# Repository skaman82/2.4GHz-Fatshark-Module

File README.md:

BUILD LOG: https://github.com/skaman82/2.4GHz-Fatshark-Module/wiki </br> </br>

# 2.4GHz-Fatshark-Module
RX28 based Fatshark RX module

- 8 channels (2414, 2432, 2450, 2468, 2490, 2510, 2390, 2370 MHz)
- RSSI display
- Fatshark button control
- Bandscan
- Finder mode
- RSSI calibration
- OSD menus
- OLED screen

Tested with following VTX models:</br>
• TBS Unify 2G4</br>
• Lawmate 2.4</br>
• FuriousFPV 2.4 VTX</br>
• Cheap low power chinese transmitter modules </br>
(no audio compatibility issues unlike the latest RX 2.4 module on the market)

# OPERATION
<b>HOME SCREEN:</b> You can change the channels by pressing the UP/DOWN keys - it works also with the google buttons (if the feature is active). If using the joystick you have to press UP/DOWN once to bring the OSD up - then you can change the channel. After no button press is registered the OSD will automatically disappear. </br>
</br>
By pressing the CENTER button you can bring up the <b>MENU</b>. With UP/DOWN you can switch between different menu items. Select EXIT to return to the home screen.</br>
</br>
<b>GOGGLE CONTROL:</b> Enables fatshark button control.</br>
</br>
<b>BANDSCAN:</b> Scans all channels and displays the RSSI values in a graph.</br>
</br>
<b>LOCK MODE:</b> If activated (lock icon in the home screen) the module will lock up after approx. 10 seconds. All controls are disabled to prevent chanel changes on acidental button press. You can temporarily UNLOCK the module by pressing the CENTER button for 3-5 seconds (the lock icon will open). After unlocking the module it will return to locked state after approx. 10 seconds.</br>
</br>
<b>FIND MODE:</b>Will show the RSSI value in a BAR (oled) or a plot (OSD). Depending on the RSSI value the beeper will beep more often and the OSD LED will blink as well indicating the direction. You can change the channel in the FIND MODE - so be sure you have the correct one. Use a directional antenna to find your model with this function.</br>
</br>
<b>AUTOSEARCH:</b> Press the CENTER button for 2 seconds to call the autosearch function. Autosearch will find the strongest channel and switch to it automatically.</br>
</br>
<b>CALIBRATION:</b> You have to run calibration to have the correct RSSI values. Just follow the instructions in the wizzard.</br>

# UPDATING THE FIRMWARE
You will need a FTDI to USB adapter to upload the module firmware. You may need to install the FTDI driver for it. Set the FTDI to 5V.

Steps to upload new firmware
1. Install Arduino IDE
2. Install the Arduino Libraries from the "Libs" folder.
3. Install the MightyCore hardware package from here: https://github.com/MCUdude/MightyCore (just follow the instructions)
4. Download the firmware and open the Code.INO file from the "Code" folder in Arduino
5. Select the hardware settings in Arduino IDE as shown in the image below
6. Connect the FTDI tool according to the plug pinout as shown in the picture and select the COM port in Arduino IDE
7. If you have the rev 06 PCB open the JUMP1 jumper on the PCB to upload code (solder it together after your upload is done).
8. Upload the code </br>
YOU ARE DONE :)

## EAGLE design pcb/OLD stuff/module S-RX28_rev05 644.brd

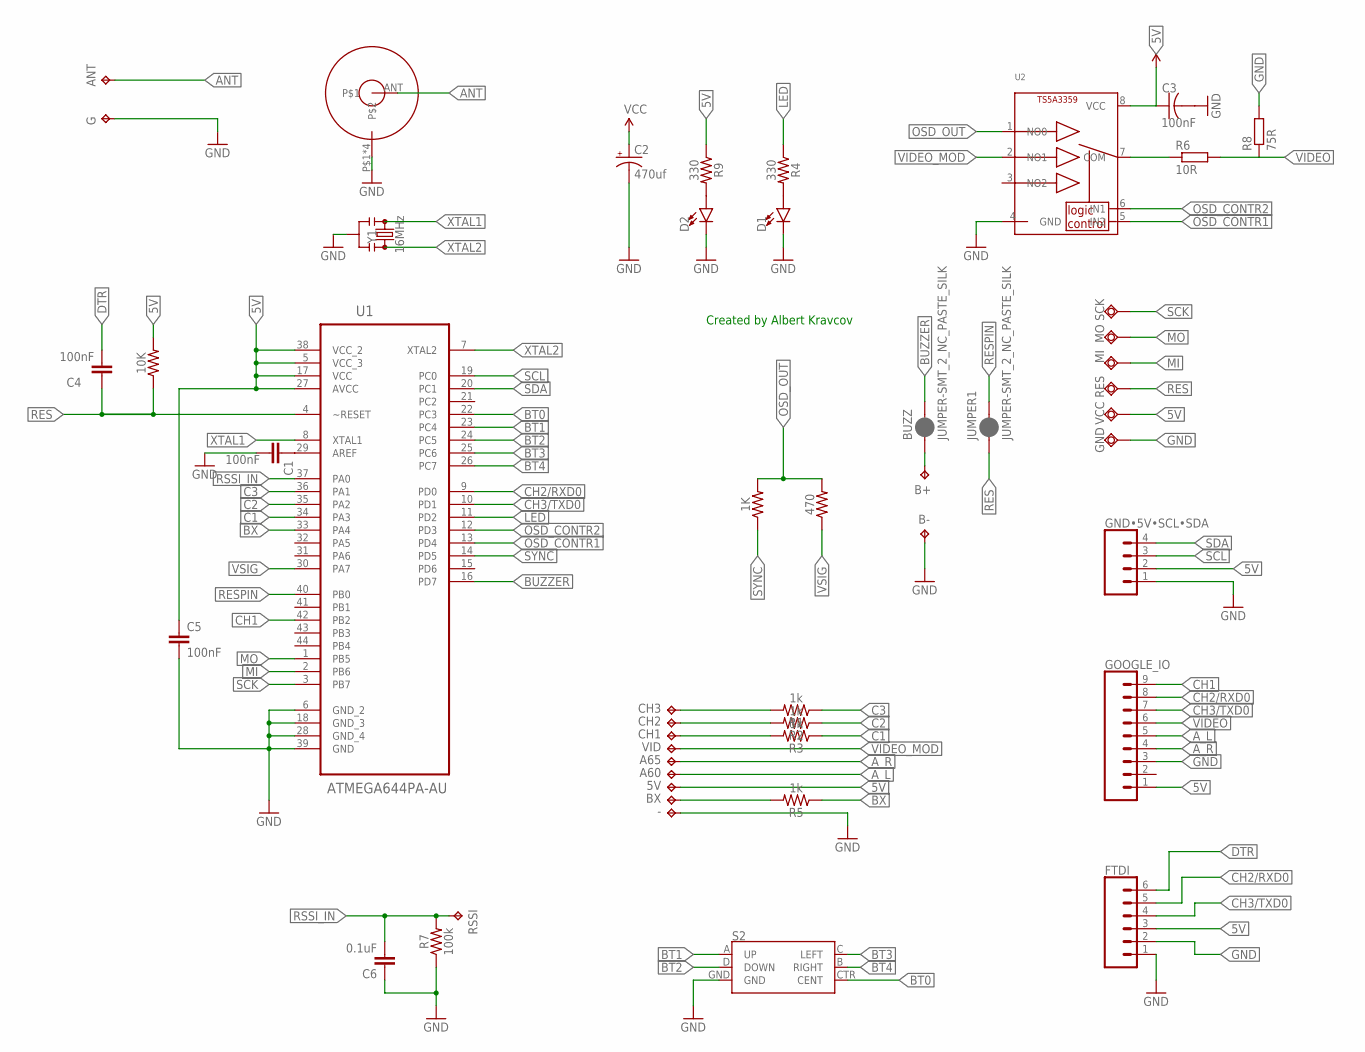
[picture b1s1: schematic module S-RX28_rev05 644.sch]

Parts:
1K, 10K, 470: 0.27OHM-0603-1/10W-1%; 0603
5V: TPTP15SQ; TP15SQ
-: TPTP15SQ; TP15SQ
A60, A65: TPTP15SQ; TP15SQ
ANT: TPTP15R; TP15R
B+: TPTP17SQ; TP17SQ
B-: TPTP17SQ; TP17SQ
BUZZ: JUMPER-SMT_2_NC_PASTE_SILK; SMT-JUMPER_2_NC_PASTE_SILK
BX: TPTP15SQ; TP15SQ
C1, C4, C5: 100nF; 0603
C2: 470uf; EIA7343
C3: 100nF; C0603
C6: 0.1uF; 0603
CH1, CH2, CH3: TPTP15SQ; TP15SQ
D1, D2: LED0603; LED-0603
FTDI: CONN_06SMD-1MM; 1X06-1MM
G: TPTP15SQ; TP15SQ
GND: GND; B1,27
GND•5V•SCL•SDA: CONN_04; 1X04
GOOGLE_IO: CONN_09; 1X09
JUMPER1: JUMPER-SMT_2_NC_PASTE_SILK; SMT-JUMPER_2_NC_PASTE_SILK
MI: TPSQB1,27; B1,27
MO: TPSQB1,27; B1,27
R1, R2, R3, R5: 1k; 0603
R4, R9: 330; 0603
R6: 10R; R0603
R7: 100k; 0603
R8: 75R; R0603
RES: TPSQB1,27; B1,27
RSSI: TPTP15SQ; TP15SQ
S2: JOYSTICK_MINI
SCK: TPSQB1,27; B1,27
U1: ATMEGA644PA-AU; QFP80P1200X1200X120-44N
U2: TS5A3359; VFSOP-8
U$1: SMA_ANTENNA; SMA_CONNECTOR
VCC: TPSQB1,27; B1,27
VID: TPTP15SQ; TP15SQ
Y1: 16MHz; RESONATOR-SMD-3.2X1.3

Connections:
5V: 5V.TP, 10K.2, C2.A (+), C3.1, C5.1, FTDI.3, GND•5V•SCL•SDA.2, GOOGLE_IO.1, R9.1, U1.5 (VCC_3), U1.17 (VCC), U1.27 (AVCC), U1.38 (VCC_2), U2.8 (VCC), VCC.TP
ANT: ANT.TP, U$1.ANT
AREF: C1.1, U1.29 (AREF)
A_L: A60.TP, GOOGLE_IO.5
A_R: A65.TP, GOOGLE_IO.4
BT0: S2.CTR (CENT), U1.22 (PC3)
BT1: S2.A (UP), U1.23 (PC4)
BT2: S2.D (DOWN), U1.24 (PC5)
BT3: S2.C (LEFT), U1.25 (PC6)
BT4: S2.B (RIGHT), U1.26 (PC7)
BUZZER: BUZZ.2, U1.16 (PD7)
BX: R5.1, U1.33 (PA4)
C1: R3.1, U1.34 (PA3)
C2: R2.1, U1.35 (PA2)
C3: R1.1, U1.36 (PA1)
CH1: GOOGLE_IO.9, U1.42 (PB2)
CH2/RXD0: FTDI.5, GOOGLE_IO.8, U1.9 (PD0)
CH3/TXD0: FTDI.4, GOOGLE_IO.7, U1.10 (PD1)
DTR: C4.2, FTDI.6
GND: -.TP, B-.TP, C1.2, C2.C (-), C3.2, C5.2, C6.1, D1.C, D2.C, FTDI.1, FTDI.2, G.TP, GND.TP, GND•5V•SCL•SDA.1, GOOGLE_IO.3, R7.1, R8.2, S2.GND, U1.6 (GND_2), U1.18 (GND_3), U1.28 (GND_4), U1.39 (GND), U2.4 (GND), U$1.P$1, U$1.P$2, U$1.P$3, U$1.P$4, Y1.2
LED: R4.1, U1.11 (PD2)
MI: MI.TP, U1.2 (PB6)
MO: MO.TP, U1.1 (PB5)
unnamed: CH3.TP, R1.2
unnamed: B+.TP, BUZZ.1
unnamed: CH2.TP, R2.2
unnamed: CH1.TP, R3.2
unnamed: BX.TP, R5.2
OSD_CONTR1: U1.13 (PD4), U2.5 (IN2)
OSD_CONTR2: U1.12 (PD3), U2.6 (IN1)
OSD_OUT: 1K.2, 470.2, U2.1 (NO0)
RED: D1.A, R4.2
RED1: D2.A, R9.2
RES: 10K.1, C4.1, JUMPER1.1, RES.TP, U1.4 (~RESET)
RESPIN: JUMPER1.2, U1.40 (PB0)
RSSI_IN: C6.2, R7.2, RSSI.TP, U1.37 (PA0)
SCK: SCK.TP, U1.3 (PB7)
SCL: GND•5V•SCL•SDA.3, U1.19 (PC0)
SDA: GND•5V•SCL•SDA.4, U1.20 (PC1)
SYNC: 1K.1, U1.14 (PD5)
VIDEO: GOOGLE_IO.6, R6.2, R8.1
VIDEOOUTPUT: R6.1, U2.7 (COM)
VIDEO_MOD: U2.2 (NO1), VID.TP
VSIG: 470.1, U1.30 (PA7)
XTAL1: U1.8 (XTAL1), Y1.1
XTAL2: U1.7 (XTAL2), Y1.3

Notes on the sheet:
Created by Albert Kravcov

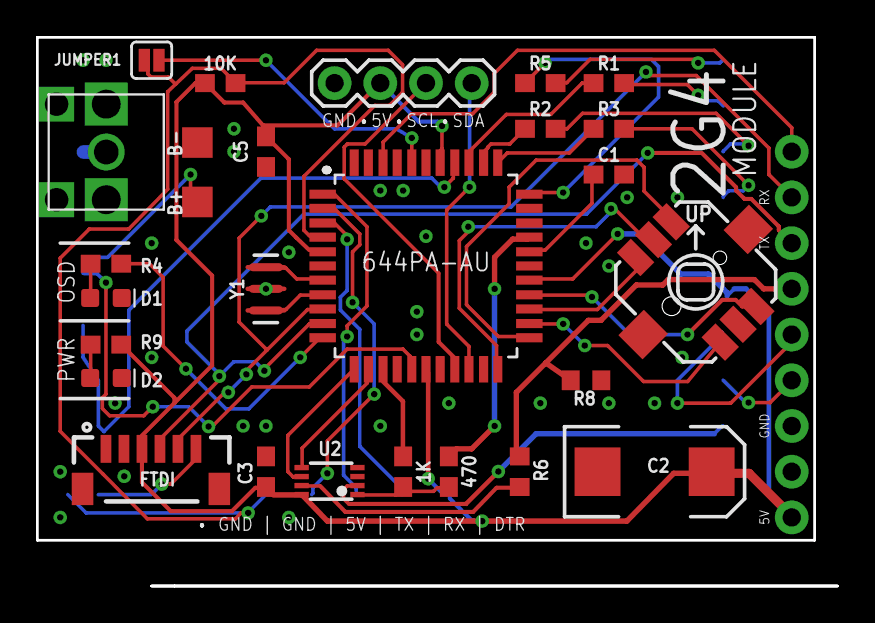
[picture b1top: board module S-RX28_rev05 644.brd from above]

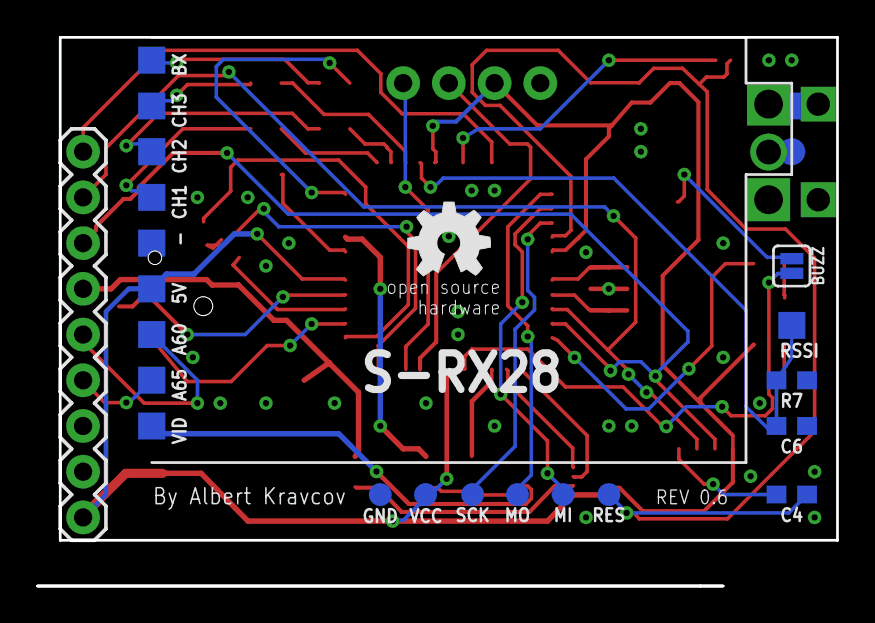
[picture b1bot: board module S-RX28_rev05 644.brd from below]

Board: 2 copper layers, 44.5 x 30.5 mm, 51 parts (24 on the bottom side), 46 nets.

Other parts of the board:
U$2: OSHW_5MM

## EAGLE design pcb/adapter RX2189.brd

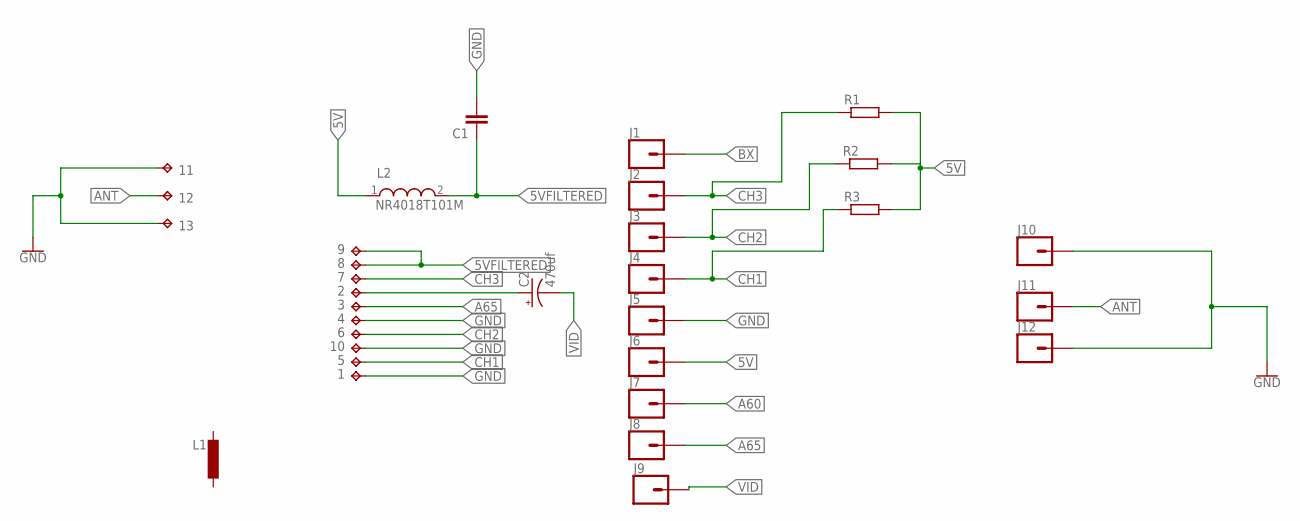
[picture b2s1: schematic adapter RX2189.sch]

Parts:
1, 2, 3, 4, 5, 6, 7, 8, 9, 10, 11, 12, 13: TPTP10SQ; TP10SQ
C1: C-EUC1206K; C1206K
C2: 470uf; EIA7343
J1, J2, J3, J4, J5, J6, J7, J8, J9, J10, J11, J12: CONN_01PTH_NO_SILK_KIT; 1X01NS_KIT
L1: L-EUWE-TPC; POWER-CHOKE_WE-TPC
L2: NR4018T101M; INDM4949X200N
R1, R2, R3: R-EU_R0603; R0603

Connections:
5V: J6.1, L2.1, R1.2, R2.2, R3.2
5VFILTERED: 8.TP, 9.TP, C1.1, L2.2
A60: J7.1
A65: 3.TP, J8.1
ANT: 12.TP, J11.1
BX: J1.1
CH1: 5.TP, J4.1, R3.1
CH2: 6.TP, J3.1, R2.1
CH3: 7.TP, J2.1, R1.1
GND: 1.TP, 4.TP, 10.TP, 11.TP, 13.TP, C1.2, J5.1, J10.1, J12.1
unnamed: 2.TP, C2.A (+)
VID: C2.C (-), J9.1

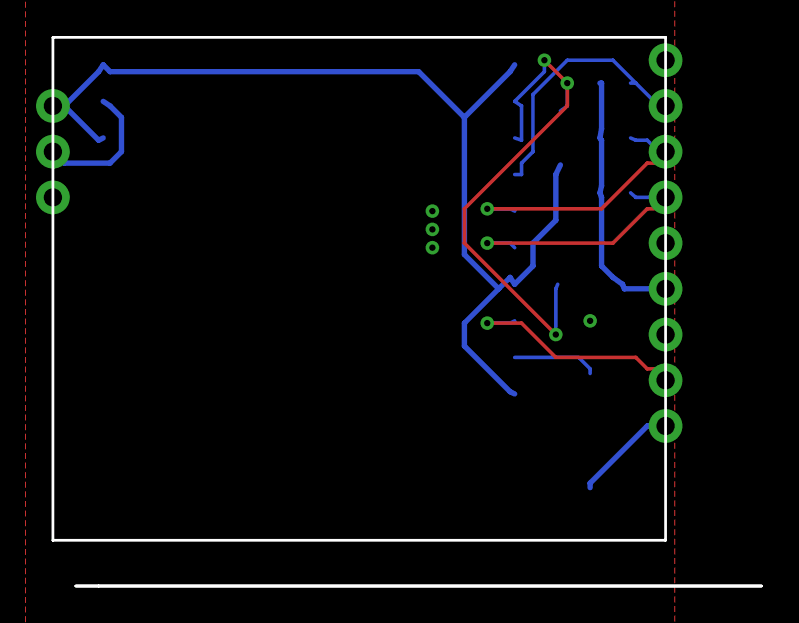
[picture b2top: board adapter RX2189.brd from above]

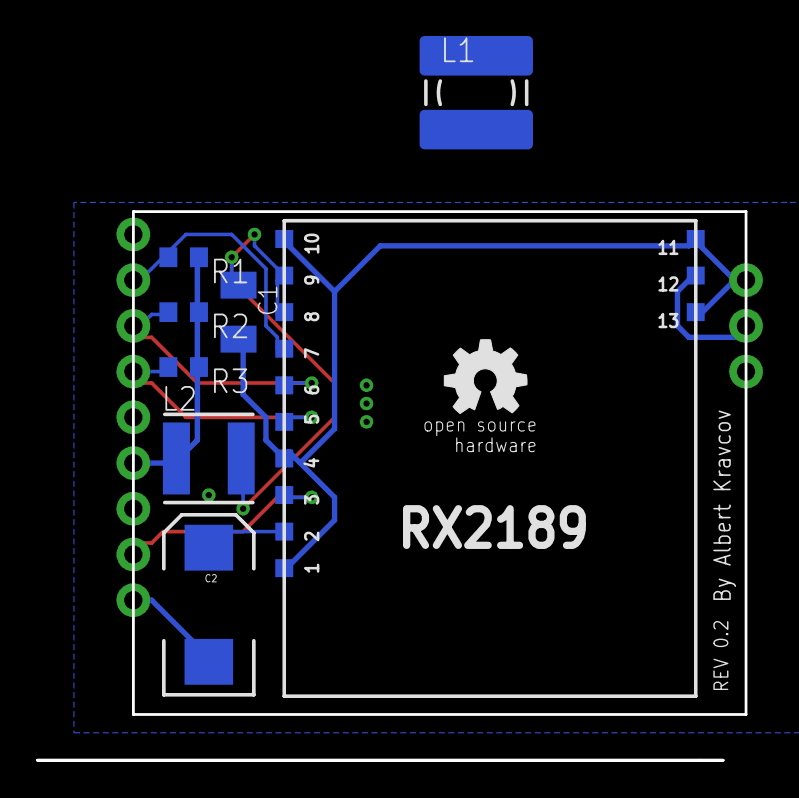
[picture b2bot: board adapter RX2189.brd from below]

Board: 2 copper layers, 34.0 x 27.9 mm, 33 parts (21 on the bottom side), 10 nets.

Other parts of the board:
U$2: OSHW_5MM

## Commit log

2019-02-28 first docs
2019-06-12 initial code commit
2019-06-13 fixing menus and cleanup
2019-06-13 Adding Libraries
2019-06-13 added docs
2019-06-13 more docs
2019-06-13 rename
2019-06-13 formatting
2019-06-14 bandscan screen
2019-06-14 UI adjustments
2019-06-14 small fixes
2019-06-14 lockmode & google button control EEPROM settings
2019-06-14 adress corrected
2019-06-14 eprom fix
2019-06-14 pin def
2019-06-17 lock mode
2019-06-18 OLED menu
2019-06-20 doc update
2019-06-20 new PCB revision
2019-06-21 fixed button bug and starting code for new display setting
2019-06-21 some new gfx
2019-06-21 lockmode fix & new bitmaps
2019-06-21 removing old code
2019-06-21 more cleanup
2019-06-21 typo fix
2019-06-21 display settings part one
2019-06-21 menu placeholders
2019-06-22 main osd screen overhaul
2019-06-22 bandscan oled screen
2019-06-23 accoustic RSSI feedback (finder mode)
2019-06-23 screen rotate function and serial tests
2019-06-29 finder oled screen
2019-07-08 fix for calibration menu
2019-08-08 added flashing LED in finder mode + google button fix
2019-08-08 OLED calibration wizzard
2019-08-09 OSD Finder Mode + New PCB revision (with mounting hole)
2019-08-09 cleanup
2019-08-15 documentation update
2019-08-15 change MIN/MAX in RSSI calibration to avoid confusion
2019-08-16 refactor channel table and bandscan
2019-08-17 module cover
2019-08-20 activate serial
2019-08-22 Fix bandscan
2019-08-23 experimantal autosearch code
2019-08-24 fixed autosearch + formatting
2019-08-24 Update Code.ino
    new calibration process
2019-08-26 Updates
    • Autosearch bugfix and UI
    • Calibration UI improvements
    • Cleaning-up old files
2019-08-26 License and Credits
2019-08-26 img update
2019-08-26 serial placeholder
2019-08-27 first draft for integrating DockKing communication protocol
2019-08-27 fixed channel index
2019-08-27 act serial
2019-08-27 more pics
2019-08-27 images
2019-08-27 filename change
2019-08-27 img size
2019-08-30 wiki images
2019-09-24 Slightly different module door for rev07+ PCBs

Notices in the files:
parts and their libraries:
SparkFun-Clocks: Licensing: Creative Commons ShareAlike 4.0 International - https://creativecommons.org/licenses/by-sa/4.0
